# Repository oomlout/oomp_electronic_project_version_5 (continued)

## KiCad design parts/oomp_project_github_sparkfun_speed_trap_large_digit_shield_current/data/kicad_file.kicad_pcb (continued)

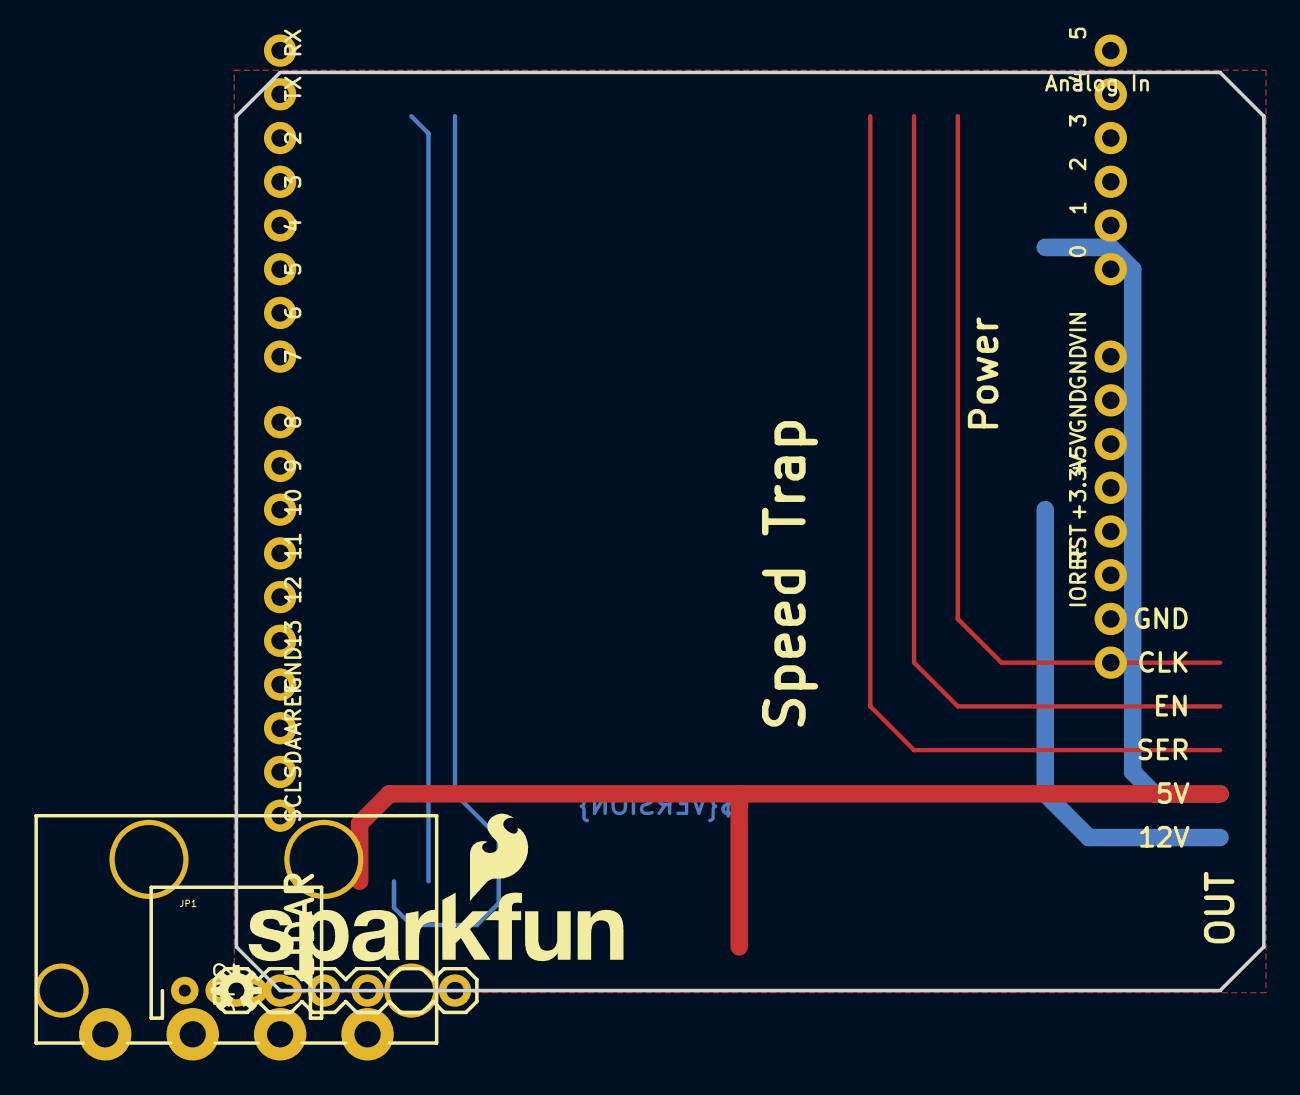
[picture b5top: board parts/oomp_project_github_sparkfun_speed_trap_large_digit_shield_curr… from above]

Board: 2 copper layers, 59.7 x 53.3 mm, 7 parts (0 on the bottom side), 8 nets.

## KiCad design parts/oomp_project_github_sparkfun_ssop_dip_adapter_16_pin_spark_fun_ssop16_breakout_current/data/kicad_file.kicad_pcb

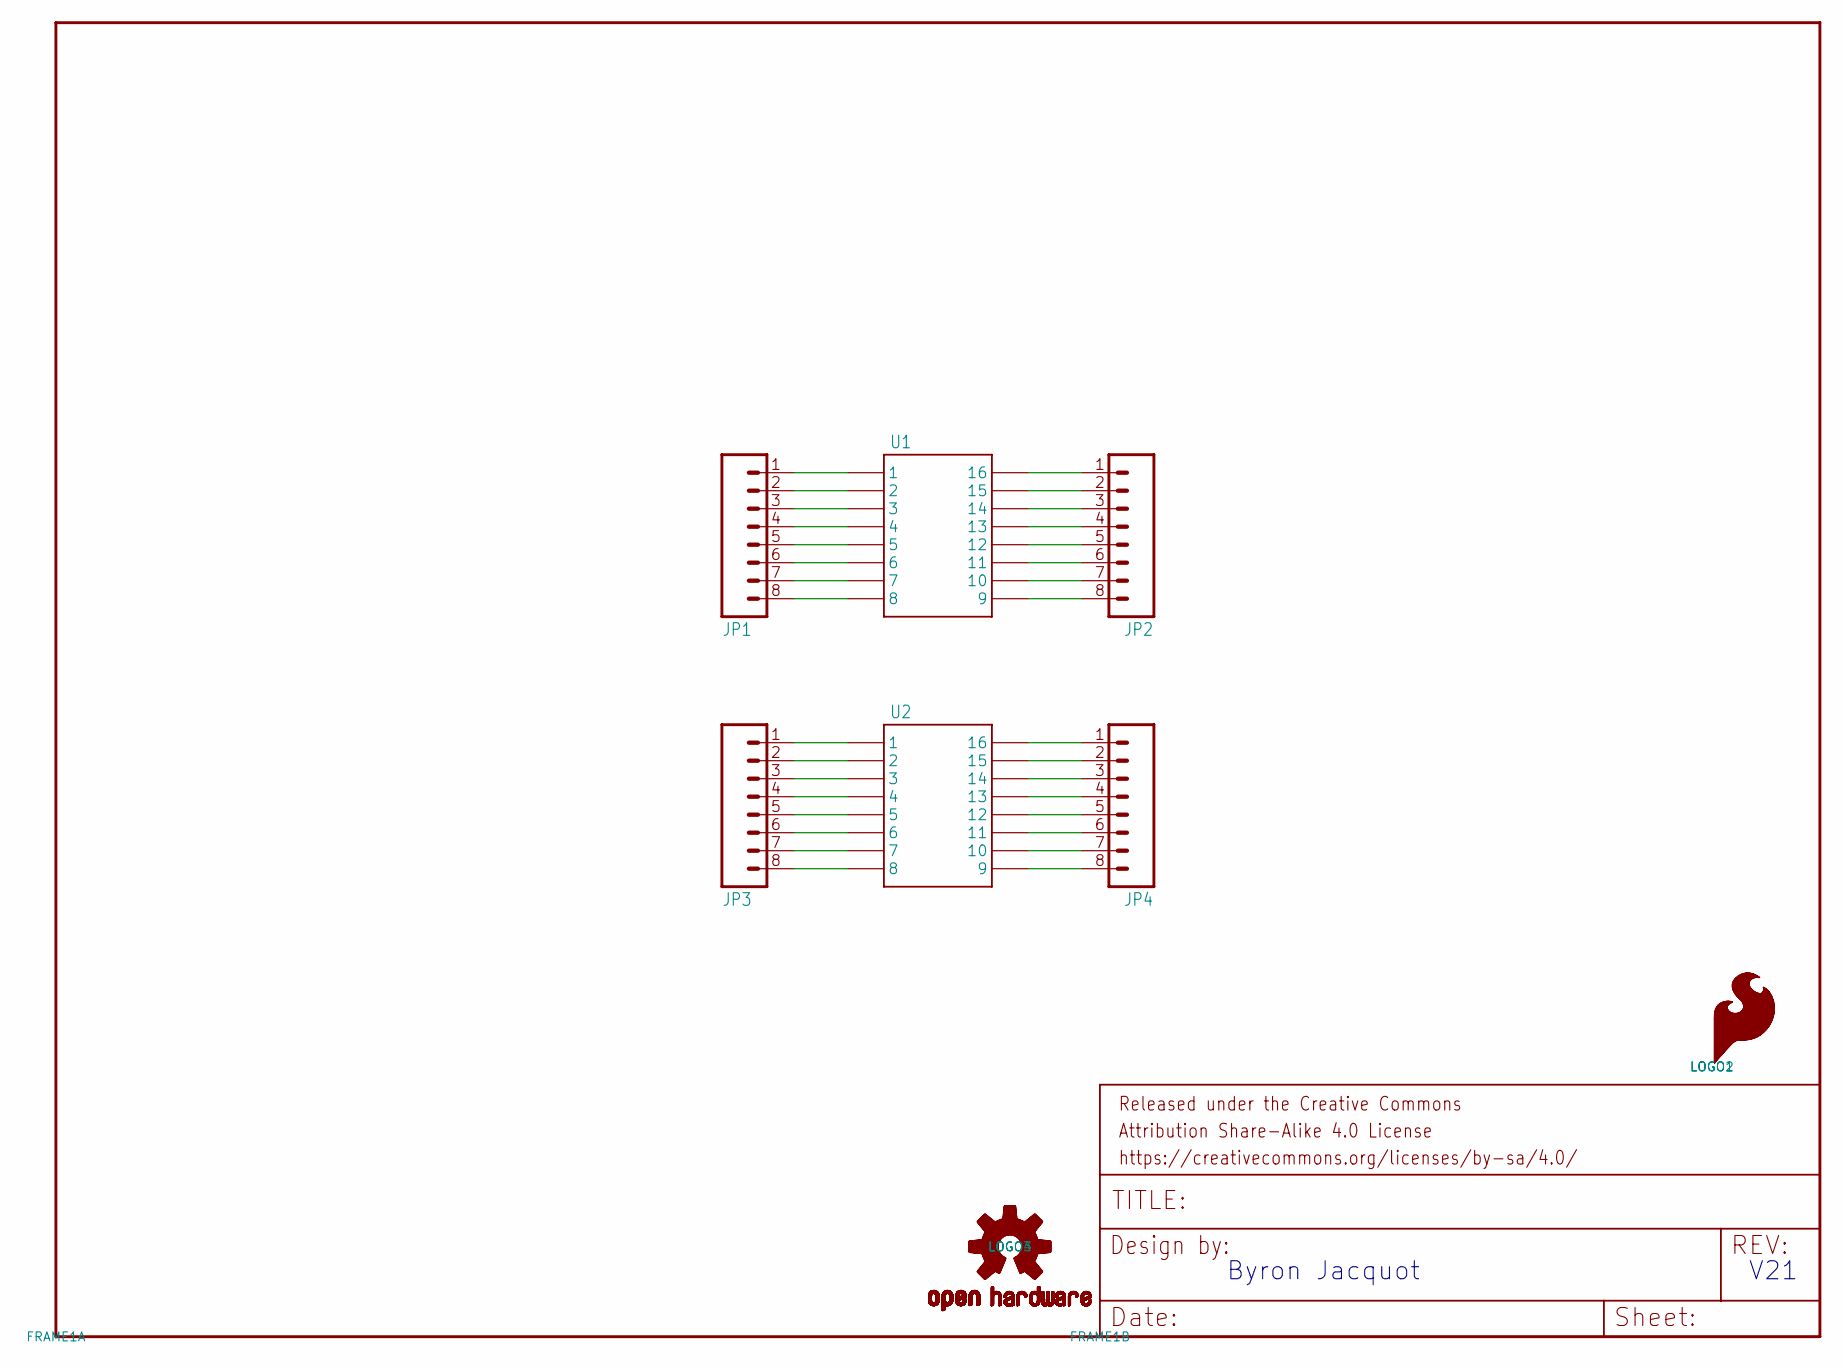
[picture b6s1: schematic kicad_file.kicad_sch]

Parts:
FRAME1: FRAME-LETTER; CREATIVE_COMMONS
JP1, JP3: M08NO_SILK; 1X08_PIN1_NO_SILK
JP2, JP4: M08NO_SILK_FEMALE_PTH; 1X08_NO_SILK
LOGO1, LOGO2: SFE_LOGO_FLAME.1_INCH; SFE_LOGO_FLAME_.1
LOGO3, LOGO4: OSHW-LOGOS; OSHW-LOGO-S
U1, U2: SSOP16

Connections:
unnamed: JP1.1, U1.P$1 (1)
unnamed: JP1.2, U1.P$2 (2)
unnamed: JP1.3, U1.P$3 (3)
unnamed: JP1.4, U1.P$4 (4)
unnamed: JP1.5, U1.P$5 (5)
unnamed: JP1.6, U1.P$6 (6)
unnamed: JP1.7, U1.P$7 (7)
unnamed: JP1.8, U1.P$8 (8)
unnamed: JP2.1, U1.P$16 (16)
unnamed: JP2.2, U1.P$15 (15)
unnamed: JP2.3, U1.P$14 (14)
unnamed: JP2.4, U1.P$13 (13)
unnamed: JP2.5, U1.P$12 (12)
unnamed: JP2.6, U1.P$11 (11)
unnamed: JP2.7, U1.P$10 (10)
unnamed: JP2.8, U1.P$9 (9)
unnamed: JP4.1, U2.P$16 (16)
unnamed: JP4.2, U2.P$15 (15)
unnamed: JP4.3, U2.P$14 (14)
unnamed: JP4.4, U2.P$13 (13)
unnamed: JP4.5, U2.P$12 (12)
unnamed: JP4.6, U2.P$11 (11)
unnamed: JP4.7, U2.P$10 (10)
unnamed: JP4.8, U2.P$9 (9)
unnamed: JP3.1, U2.P$1 (1)
unnamed: JP3.2, U2.P$2 (2)
unnamed: JP3.3, U2.P$3 (3)
unnamed: JP3.4, U2.P$4 (4)
unnamed: JP3.5, U2.P$5 (5)
unnamed: JP3.6, U2.P$6 (6)
unnamed: JP3.7, U2.P$7 (7)
unnamed: JP3.8, U2.P$8 (8)

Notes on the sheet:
V21
Byron Jacquot

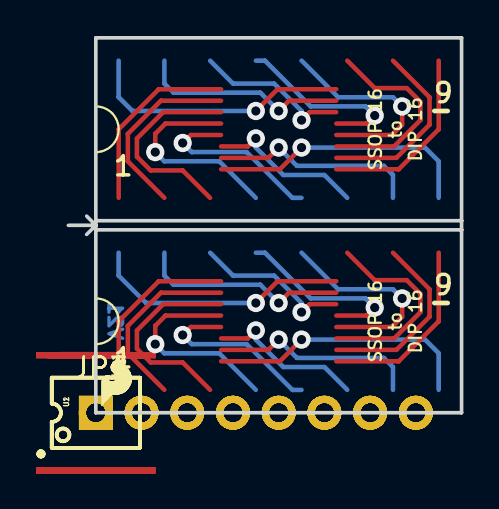
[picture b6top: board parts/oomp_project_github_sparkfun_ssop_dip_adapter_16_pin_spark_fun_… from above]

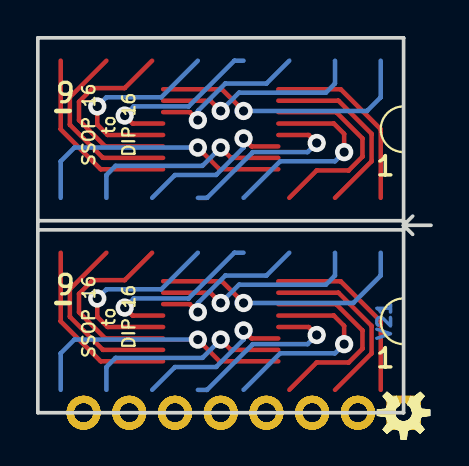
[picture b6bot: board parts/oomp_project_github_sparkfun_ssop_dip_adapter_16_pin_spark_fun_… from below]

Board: 2 copper layers, 21.8 x 20.8 mm, 11 parts (2 on the bottom side), 32 nets.

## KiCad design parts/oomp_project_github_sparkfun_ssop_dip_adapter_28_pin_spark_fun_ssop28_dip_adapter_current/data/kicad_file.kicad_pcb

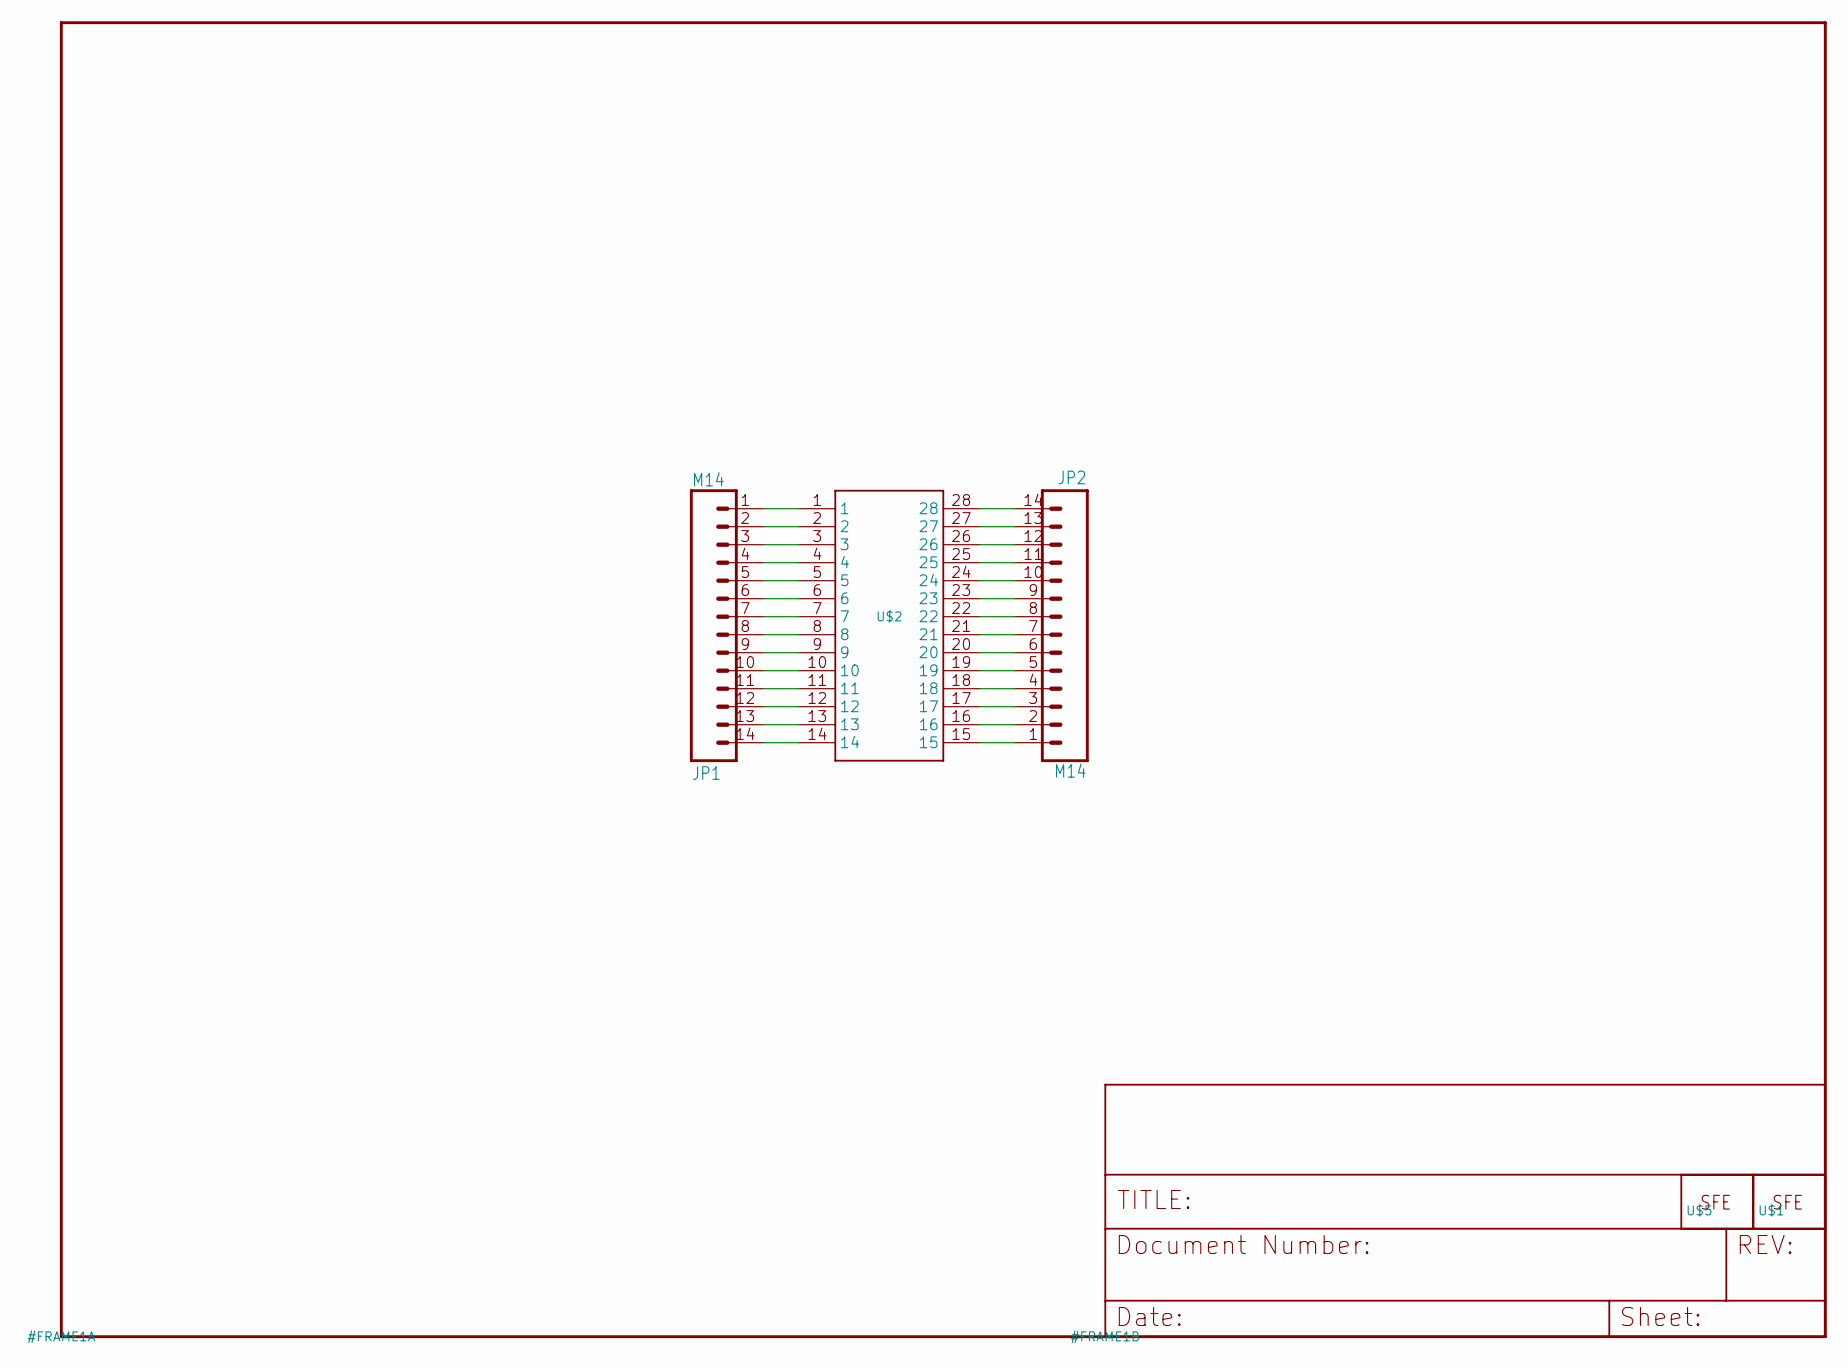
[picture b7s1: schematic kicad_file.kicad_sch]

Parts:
JP1, JP2: M14; 1X14
U$1: LOGO-SFESK; SFE-LOGO-FLAME
U$2: SSOP28; SSOP28DB
U$5: LOGO-SFENEW; SFE-NEW-WEBLOGO

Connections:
unnamed: JP2.1, U$2.15
unnamed: JP2.2, U$2.16
unnamed: JP2.3, U$2.17
unnamed: JP2.4, U$2.18
unnamed: JP2.5, U$2.19
unnamed: JP2.6, U$2.20
unnamed: JP2.7, U$2.21
unnamed: JP2.8, U$2.22
unnamed: JP2.9, U$2.23
unnamed: JP2.10, U$2.24
unnamed: JP2.11, U$2.25
unnamed: JP2.12, U$2.26
unnamed: JP2.13, U$2.27
unnamed: JP2.14, U$2.28
unnamed: JP1.1, U$2.1
unnamed: JP1.2, U$2.2
unnamed: JP1.3, U$2.3
unnamed: JP1.4, U$2.4
unnamed: JP1.5, U$2.5
unnamed: JP1.6, U$2.6
unnamed: JP1.7, U$2.7
unnamed: JP1.8, U$2.8
unnamed: JP1.9, U$2.9
unnamed: JP1.10, U$2.10
unnamed: JP1.11, U$2.11
unnamed: JP1.12, U$2.12
unnamed: JP1.13, U$2.13
unnamed: JP1.14, U$2.14

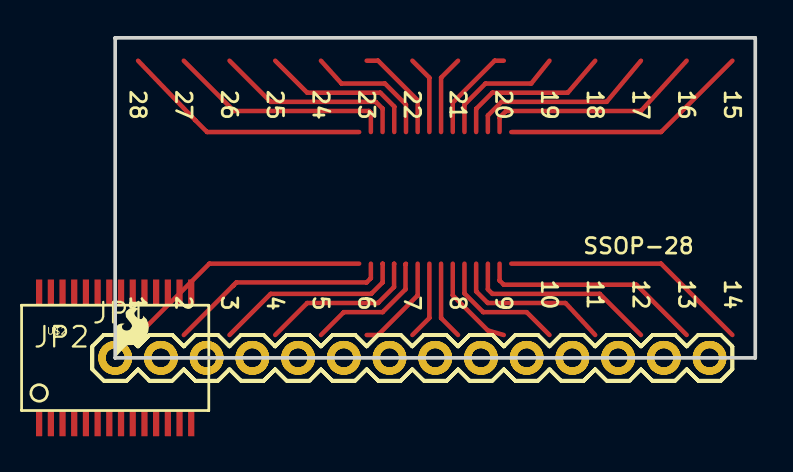
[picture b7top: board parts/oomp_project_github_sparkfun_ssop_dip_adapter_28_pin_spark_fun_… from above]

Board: 2 copper layers, 35.6 x 17.8 mm, 5 parts (1 on the bottom side), 28 nets.

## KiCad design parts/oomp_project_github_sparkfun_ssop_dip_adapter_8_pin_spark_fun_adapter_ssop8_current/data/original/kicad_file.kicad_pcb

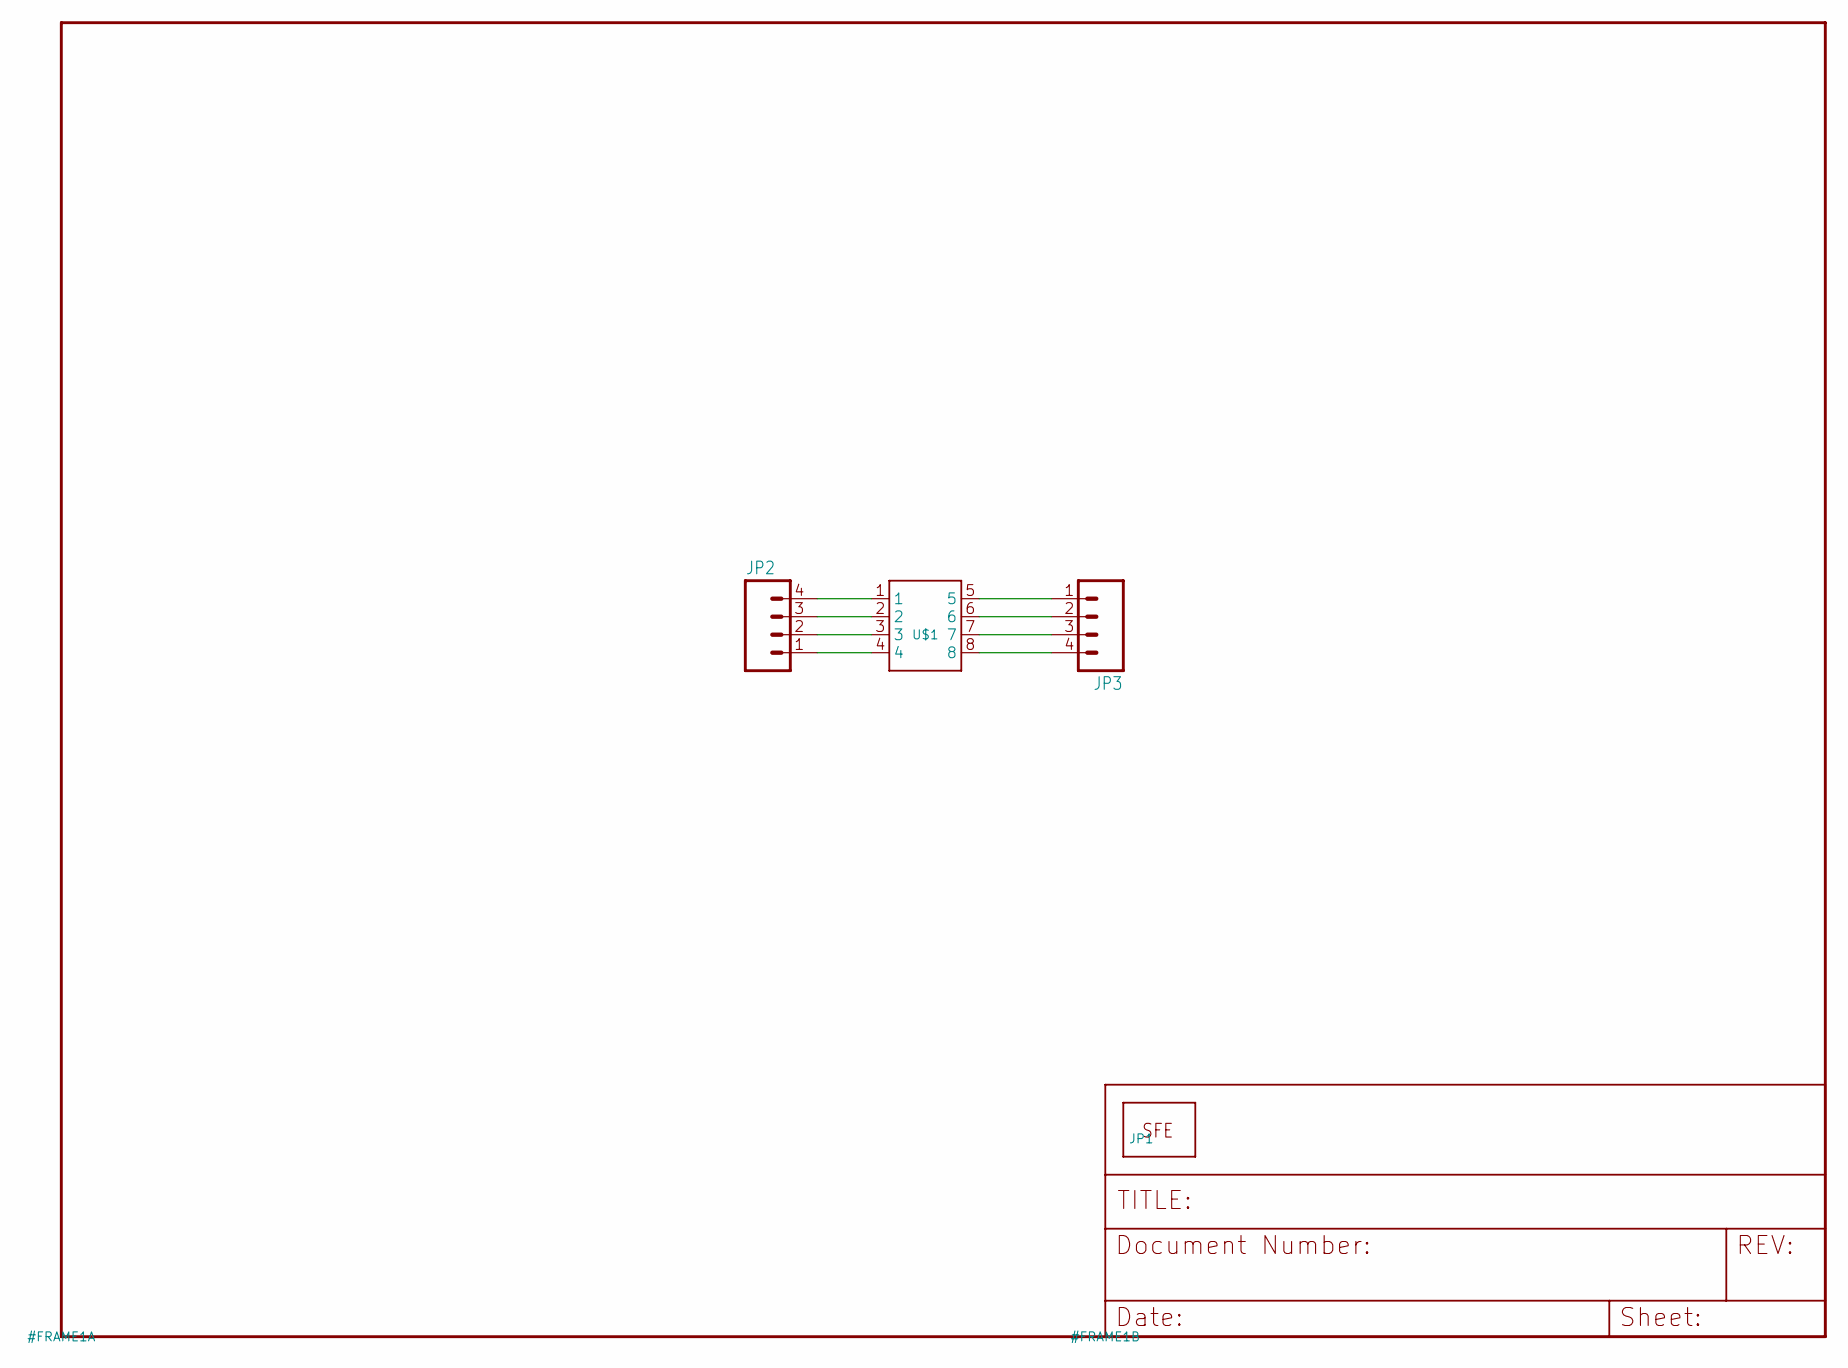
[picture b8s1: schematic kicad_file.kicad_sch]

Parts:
JP1: LOGO-SFESK; SFE-LOGO-FLAME
JP2, JP3: M04PTH; 1X04
U$1: SSOP8

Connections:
unnamed: JP2.1, U$1.4
unnamed: JP2.2, U$1.3
unnamed: JP2.3, U$1.2
unnamed: JP2.4, U$1.1
unnamed: JP3.1, U$1.5
unnamed: JP3.2, U$1.6
unnamed: JP3.3, U$1.7
unnamed: JP3.4, U$1.8

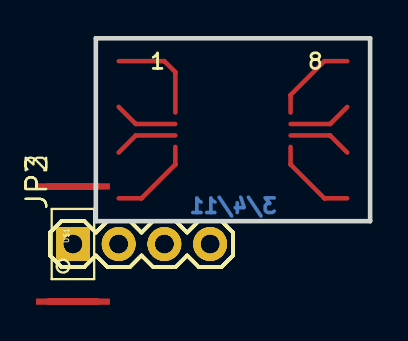
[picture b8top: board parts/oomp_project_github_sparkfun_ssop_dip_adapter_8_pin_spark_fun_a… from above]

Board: 2 copper layers, 15.2 x 10.2 mm, 4 parts (1 on the bottom side), 8 nets.
